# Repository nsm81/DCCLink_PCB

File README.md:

# DCCLink_PCB

The DCCLink board connects the DCC track signal to an Arduino. It also provides a regulated 5V supply from the track. It does not provide DCC ACK support for PoM (Programming on the main).

The board is designed and made in KiCad 6.0.

I reccomend using the AP_DCC_Library written by Aiko Pras.

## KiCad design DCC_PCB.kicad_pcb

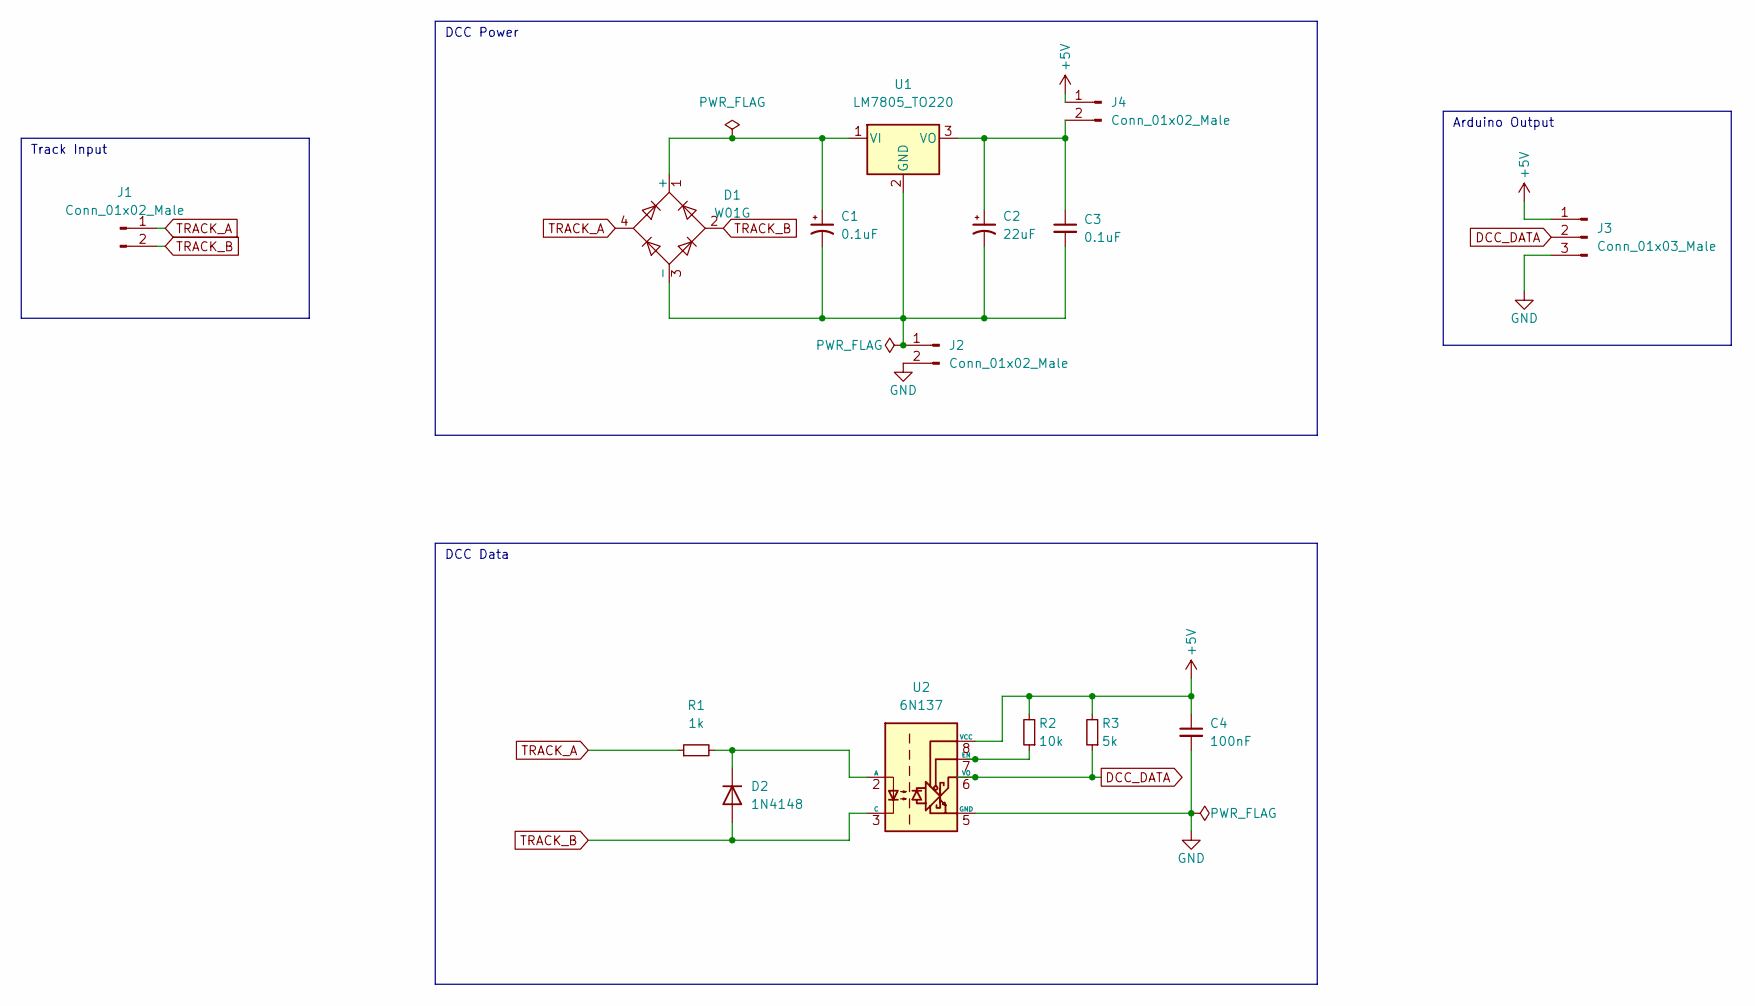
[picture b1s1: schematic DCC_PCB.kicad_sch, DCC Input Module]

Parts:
C1: 0.1uF; CP_Radial_D5.0mm_P2.00mm
C2: 22uF; CP_Radial_D4.0mm_P1.50mm
C3: 0.1uF; C_Disc_D5.0mm_W2.5mm_P5.00mm
C4: 100nF; C_Disc_D5.0mm_W2.5mm_P5.00mm
D1: W01G; Diode_Bridge_Round_D9.8mm
D2: 1N4148; D_DO-35_SOD27_P2.54mm_Vertical_AnodeUp
J1, J2, J4: Conn_01x02_Male; PinHeader_1x02_P2.54mm_Vertical
J3: Conn_01x03_Male; PinHeader_1x03_P2.54mm_Vertical
R1: 1k; R_Axial_DIN0204_L3.6mm_D1.6mm_P1.90mm_Vertical
R2: 10k; R_Axial_DIN0204_L3.6mm_D1.6mm_P1.90mm_Vertical
R3: 5k; R_Axial_DIN0204_L3.6mm_D1.6mm_P1.90mm_Vertical
U1: LM7805_TO220; TO-220-3_Vertical
U2: 6N137; DIP-8_W7.62mm

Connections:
+5V: C4.1, J3.1, J4.1, R2.2, R3.2, U2.8 (VCC)
DCC_DATA: J3.2, R3.1, U2.6 (VO)
GND: C4.2, J2.2, J3.3, U2.5 (GND)
unnamed: C1.1, D1.1 (+), U1.1 (VI)
unnamed: C1.2, C2.2, C3.2, D1.3 (-), J2.1, U1.2 (GND)
unnamed: C2.1, C3.1, J4.2, U1.3 (VO)
unnamed: D2.1 (K), R1.2, U2.2 (A)
unnamed: R2.1, U2.7 (EN)
TRACK_A: D1.4, J1.1, R1.1
TRACK_B: D1.2, D2.2 (A), J1.2, U2.3 (C)

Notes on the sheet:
DCC Power
Arduino Output
DCC Data
Track Input

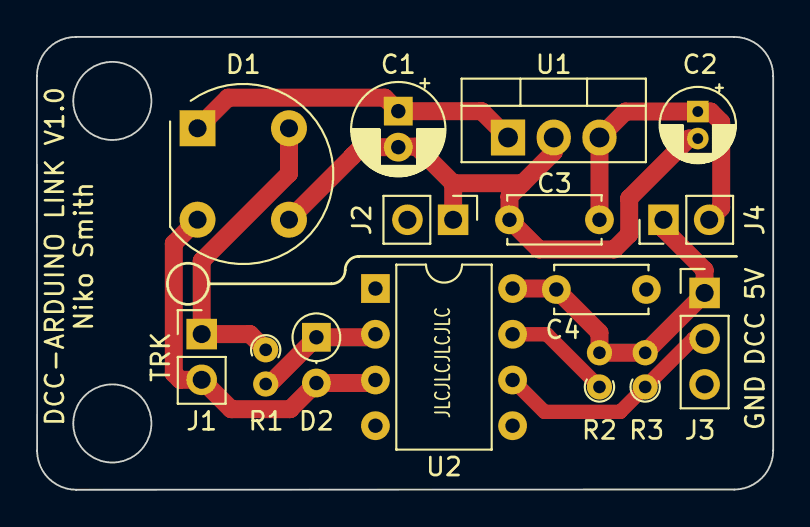
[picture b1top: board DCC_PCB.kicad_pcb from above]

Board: 2 copper layers, 40.9 x 25.2 mm, 15 parts (0 on the bottom side), 10 nets.

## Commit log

2022-03-14 Create LICENSE
2022-03-23 Modified Schematic
